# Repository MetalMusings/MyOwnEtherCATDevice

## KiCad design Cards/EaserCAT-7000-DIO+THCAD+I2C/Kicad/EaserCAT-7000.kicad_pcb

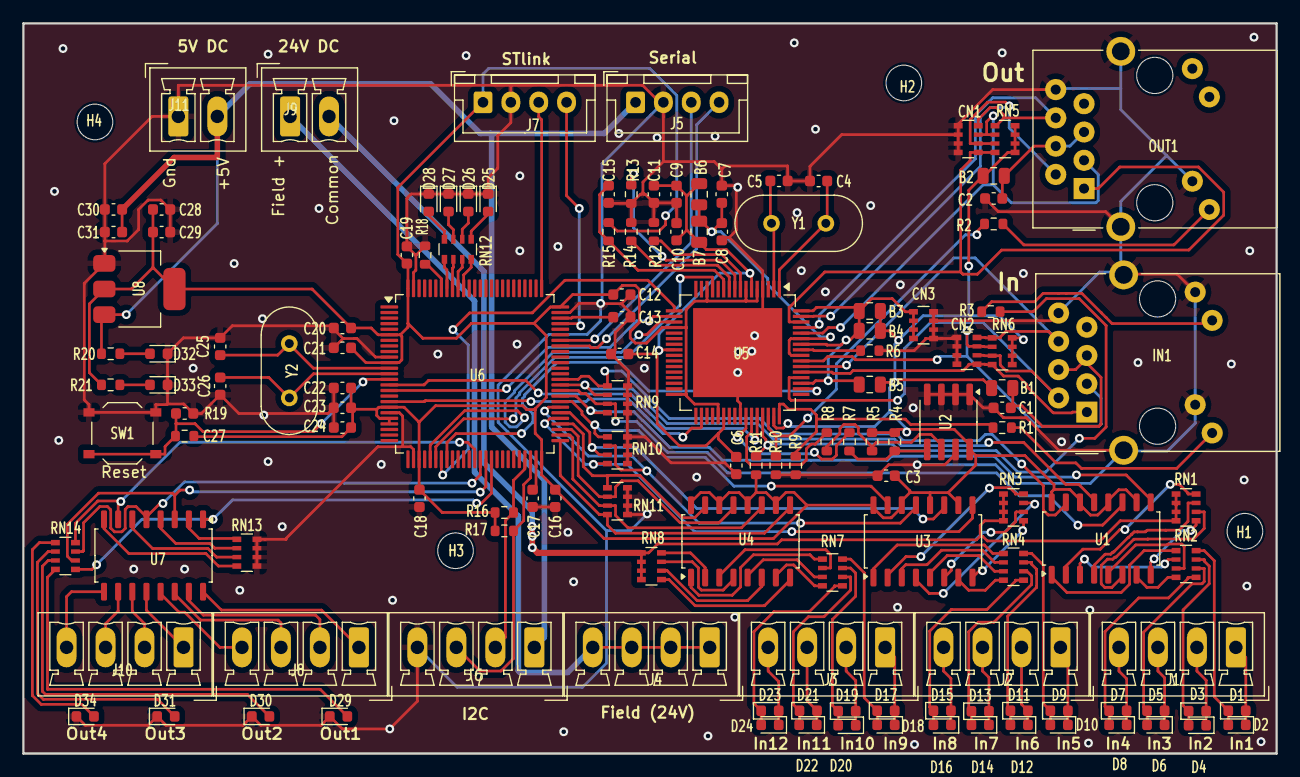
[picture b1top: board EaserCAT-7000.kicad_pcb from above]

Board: 2 copper layers, 112.5 x 65.6 mm, 138 parts (0 on the bottom side), 144 nets.

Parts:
B1, B2, B3, B4, B5, B6, B7: BLM18EG221S; C_0805_2012Metric
C1, C2, C3, C6, C8, C10, C12, C14, C15, C16, C18, C19, C20, C21, C22, C23, C24, C27, C29, C31: 0.1uF; C_0603_1608Metric
C4, C5: 20pF; C_0603_1608Metric
C7: 2uF; C_0603_1608Metric
C9: 1uF; C_0603_1608Metric
C11: 470pF; C_0603_1608Metric
C13, C17: 2.2uF; C_0603_1608Metric
C25, C26: 22pF; C_0603_1608Metric
C28, C30: 10uF; C_0603_1608Metric
CN1, CN2: 10pF; R_Array_Convex_4x0603
CN3: 0.1uF; R_Array_Convex_4x0603
D1, D3, D5, D7, D9, D11, D13, D15, D17, D19, D21, D23: Yellow led; LED_0603_1608Metric
D2, D4, D6, D8, D10, D12, D14, D16, D18, D20, D22, D24, D27: Red led; LED_0603_1608Metric
D25: Green led; LED_0603_1608Metric
D26: Orange led; LED_0603_1608Metric
D28: Blue led; LED_0603_1608Metric
D29, D30, D31, D34: White; LED_0603_1608Metric
D32, D33: Blue; LED_0603_1608Metric
H1, H2, H3, H4: MountingHole; MountingHole_3.2mm_M3_ISO14580
IN1: J0011D01BNL; PulseJack JB0011D01BNL
J1: In1-4; PhoenixContact_MCV_1,5_4-G-3.5_1x04_P3.50mm_Vertical
J2: In5-8; PhoenixContact_MCV_1,5_4-G-3.5_1x04_P3.50mm_Vertical
J3: In9-12; PhoenixContact_MCV_1,5_4-G-3.5_1x04_P3.50mm_Vertical
J4: 24V_Common; PhoenixContact_MCV_1,5_4-G-3.5_1x04_P3.50mm_Vertical
J5: Serial usart1; JST_XH_B4B-XH-A_1x04_P2.50mm_Vertical
J6: I2C; PhoenixContact_MCV_1,5_4-G-3.5_1x04_P3.50mm_Vertical
J7: STLINK; JST_XH_B4B-XH-A_1x04_P2.50mm_Vertical
J8: Output1-2; PhoenixContact_MCV_1,5_4-G-3.5_1x04_P3.50mm_Vertical
J9: 24V Field; PhoenixContact_MCV_1,5_2-G-3.5_1x02_P3.50mm_Vertical
J10: Output3-4; PhoenixContact_MCV_1,5_4-G-3.5_1x04_P3.50mm_Vertical
J11: 5V input; PhoenixContact_MCV_1,5_2-G-3.5_1x02_P3.50mm_Vertical
OUT1: J0011D01BNL; PulseJack JB0011D01BNL
R1, R2, R3, R19: 1k; R_0603_1608Metric
R4, R5, R16, R17, R21: 2k; R_0603_1608Metric
R6: 12.1k; R_0603_1608Metric
R7, R8: 22; R_0603_1608Metric
R9, R10, R11, R12, R13, R14, R15: 10k; R_0603_1608Metric
R18: 100k; R_0603_1608Metric
R20: 4k7; R_0603_1608Metric
RN1, RN3, RN8, RN12: 1k; R_Array_Convex_4x0603
RN2, RN4, RN7, RN14: 4k7; R_Array_Convex_4x0603
RN5, RN6: 49.9; R_Array_Convex_4x0603
RN9, RN10, RN11: 39k; R_Array_Convex_4x0603
RN13: 330; R_Array_Convex_4x0603
SW1: SW_Push; SW_Push_1P1T_XKB_TS-1187A
U1, U3, U4, U7: TLP292-4; SOIC-16_4.55x10.3mm_P1.27mm
U2: AT24CS32-SSHM; SOIC-8_3.9x4.9mm_P1.27mm
U5: LAN9252_PT; TQFP-64-1EP_10x10mm_P0.5mm_EP8x8mm
U6: STM32F407VGT6; LQFP-100_14x14mm_P0.5mm
U8: AMS1117-3.3; SOT-223-3_TabPin2
Y1: 25MHz; Crystal_HC49-4H_Vertical
Y2: 8 MHz; Crystal_HC49-4H_Vertical

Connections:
24V_COMMON: J9.2, RN1.5 (R4.2), RN1.6 (R3.2), RN1.7 (R2.2), RN1.8 (R1.2), RN3.5 (R4.2), RN3.6 (R3.2), RN3.7 (R2.2), RN3.8 (R1.2), RN8.5 (R4.2), RN8.6 (R3.2), RN8.7 (R2.2), RN8.8 (R1.2)
24V_FIELD: J4.1, J4.2, J4.3, J4.4, J9.1
+1V2: B6.1, B7.1, C6.2, C9.1, C10.2, C11.1, C14.2, U5.6 (VDDCR), U5.24 (VDDCR), U5.38 (VDDCR)
+3.3V: B1.1, B2.1, B3.1, B4.1, B5.1, C3.2, C12.1, C16.1, C18.1, C19.1, C20.1, C21.1, C22.1, C23.1, C24.1, C28.1, C29.1, J7.1, R4.1, R5.1, R11.1, R15.1, R16.1, R17.1, R19.2, R21.1, RN5.1 (R1.1), RN5.2 (R2.1), RN5.3 (R3.1), RN5.4 (R4.1), RN6.1 (R1.1), RN6.2 (R2.1), RN6.3 (R3.1), RN6.4 (R4.1), U1.10, U1.12, U1.14, U1.16, U2.8 (VCC), U3.10, U3.12, U3.14, U3.16, U4.10, U4.12, U4.14, U4.16, U5.5 (VDD33), U5.7 (REG_EN), U5.14 (VDDIO), U5.20 (VDDIO), U5.32 (VDDIO), U5.37 (VDDIO), U5.47 (VDDIO), U6.6 (VBAT), U6.11 (VDD), U6.19 (VDD), U6.21 (VREF+), U6.22 (VDDA), U6.28 (VDD), U6.50 (VDD), U6.75 (VDD), U6.100 (VDD), U8.2 (VO)
+3.3VA: B3.2, B4.2, B5.2, CN3.1 (R1.1), CN3.2 (R2.1), CN3.3 (R3.1), CN3.4 (R4.1), U5.51 (VDD33TXRX1), U5.58 (VDD33BIAS), U5.64 (VDD33TXRX2)
+5V: C30.1, C31.1, J5.1, J6.1, J11.2, R20.1, U8.3 (VI)
FXLOSA: R13.1, U5.9 (FXSDA/FXLOSA/~FXSDENA)
FXLOSB: R14.1, U5.10 (FXSDB/FXLOSB/~FXSDENB)
FXLOSEN: R12.1, U5.8 (~FXLOSEN)
GND: C1.1, C2.1, C3.1, C4.1, C5.1, C6.1, C7.2, C8.2, C9.2, C10.1, C11.2, C12.2, C13.1, C14.1, C15.1, C16.2, C17.1, C18.2, C19.2, C20.2, C21.2, C22.2, C23.2, C24.2, C25.1, C26.1, C27.1, C28.2, C29.2, C30.2, C31.2, CN1.5 (R4.2), CN1.6 (R3.2), CN1.7 (R2.2), CN1.8 (R1.2), CN2.5 (R4.2), CN2.6 (R3.2), CN2.7 (R2.2), CN2.8 (R1.2), CN3.5 (R4.2), CN3.6 (R3.2), CN3.7 (R2.2), CN3.8 (R1.2), D25.1 (K), D26.1 (K), D27.1 (K), D28.1 (K), D29.1 (K), D30.1 (K), D31.1 (K), D32.1 (K), D33.1 (K), D34.1 (K), IN1.8 (CHS_GND), IN1.10, IN1.12, IN1.SH (CHS_GND), J5.2, J6.4, J7.2, J11.1, OUT1.8 (CHS_GND), OUT1.10, OUT1.SH (CHS_GND), R6.1, R9.2, R10.2, R12.2, R13.2, R14.2, R18.1, RN9.5 (R4.2), RN9.6 (R3.2), RN9.7 (R2.2), RN9.8 (R1.2), RN10.5 (R4.2), RN10.6 (R3.2), RN10.7 (R2.2), RN10.8 (R1.2), RN11.5 (R4.2), RN11.6 (R3.2), RN11.7 (R2.2), RN11.8 (R1.2), RN13.5 (R4.2), RN13.6 (R3.2), RN13.7 (R2.2), RN13.8 (R1.2), SW1.1, U2.1 (A0), U2.2 (A1), U2.3 (A2), U2.4 (GND), U2.7 (WP), U5.4 (OSCVSS), U5.41 (TESTMODE), U5.65 (VSS), U6.10 (VSS), U6.20 (VSSA), U6.27 (VSS), U6.74 (VSS), U6.99 (VSS), U8.1 (GND)
I2C2_SCL: J6.2, R16.2, U6.47 (PB10)
I2C2_SDA: J6.3, R17.2, U6.48 (PB11)
I2C_SCL: R8.1, U5.43 (EESCL/TCK)
I2C_SDA: R7.1, U5.42 (EESDA/TMS)
IN0: RN9.1 (R1.1), U1.15, U6.62 (PD15)
IN1: RN9.2 (R2.1), U1.13, U6.61 (PD14)
IN2: RN9.3 (R3.1), U1.11, U6.60 (PD13)
IN3: RN9.4 (R4.1), U1.9, U6.59 (PD12)
IN4: RN10.1 (R1.1), U3.15, U6.58 (PD11)
IN5: RN10.2 (R2.1), U3.13, U6.57 (PD10)
IN6: RN10.3 (R3.1), U3.11, U6.56 (PD9)
IN7: RN10.4 (R4.1), U3.9, U6.55 (PD8)
IN8: RN11.1 (R1.1), U4.15, U6.54 (PB15)
IN9: RN11.2 (R2.1), U4.13, U6.53 (PB14)
IN10: RN11.3 (R3.1), U4.11, U6.52 (PB13)
IN11: RN11.4 (R4.1), U4.9, U6.51 (PB12)
IRQ: U5.44 (IRQ), U6.15 (PC0)
LINKACTLED0: R1.1, R9.1, U5.48 (LINKACTLED0/TDO/~CHIP_MODE0)
LINKACTLED1: R2.1, R10.1, U5.46 (LINKACTLED1/TDI/~CHIP_MODE1)
unnamed: D1.2 (A), D2.1 (K), J1.1
unnamed: D1.1 (K), D2.2 (A), RN2.8 (R1.2)
unnamed: D3.2 (A), D4.1 (K), J1.2
unnamed: D3.1 (K), D4.2 (A), RN2.7 (R2.2)
unnamed: D5.2 (A), D6.1 (K), J1.3
unnamed: D5.1 (K), D6.2 (A), RN2.6 (R3.2)
unnamed: D7.2 (A), D8.1 (K), J1.4
unnamed: D7.1 (K), D8.2 (A), RN2.5 (R4.2)
unnamed: D9.1 (K), D10.2 (A), RN4.8 (R1.2)
unnamed: D9.2 (A), D10.1 (K), J2.1
unnamed: D11.2 (A), D12.1 (K), J2.2
unnamed: D11.1 (K), D12.2 (A), RN4.7 (R2.2)
unnamed: D13.2 (A), D14.1 (K), J2.3
unnamed: D13.1 (K), D14.2 (A), RN4.6 (R3.2)
unnamed: D15.2 (A), D16.1 (K), J2.4
unnamed: D15.1 (K), D16.2 (A), RN4.5 (R4.2)
unnamed: D17.2 (A), D18.1 (K), J3.1
unnamed: D17.1 (K), D18.2 (A), RN7.8 (R1.2)
unnamed: D19.2 (A), D20.1 (K), J3.2
unnamed: D19.1 (K), D20.2 (A), RN7.7 (R2.2)
unnamed: D21.2 (A), D22.1 (K), J3.3
unnamed: D21.1 (K), D22.2 (A), RN7.6 (R3.2)
unnamed: D23.2 (A), D24.1 (K), J3.4
unnamed: D23.1 (K), D24.2 (A), RN7.5 (R4.2)
unnamed: D25.2 (A), RN12.5 (R4.2)
unnamed: D26.2 (A), RN12.6 (R3.2)
unnamed: D27.2 (A), RN12.7 (R2.2)
unnamed: D28.2 (A), RN12.8 (R1.2)
unnamed: D34.2 (A), RN14.5 (R4.2)
unnamed: D31.2 (A), RN14.6 (R3.2)
unnamed: D30.2 (A), RN14.7 (R2.2)
unnamed: D32.2 (A), R20.2
unnamed: D33.2 (A), R21.2
unnamed: D29.2 (A), RN14.8 (R1.2)
unnamed: IN1.9, R1.2
unnamed: IN1.11, R3.2
unnamed: B1.2, C1.2, IN1.4 (TCT), IN1.5 (RCT)
unnamed: J8.1, U7.16
unnamed: J8.2, U7.15
unnamed: J8.3, U7.14
unnamed: J8.4, U7.13
unnamed: J10.1, U7.12
unnamed: J10.2, U7.11
unnamed: J10.3, U7.10
unnamed: J10.4, U7.9
unnamed: OUT1.9, R2.2
unnamed: B2.2, C2.2, OUT1.4 (TCT), OUT1.5 (RCT)
unnamed: RN1.1 (R1.1), U1.8
unnamed: RN1.2 (R2.1), U1.6
unnamed: RN1.3 (R3.1), U1.4
unnamed: RN1.4 (R4.1), U1.2
unnamed: RN2.1 (R1.1), U1.1
unnamed: RN2.2 (R2.1), U1.3
unnamed: RN2.3 (R3.1), U1.5
unnamed: RN2.4 (R4.1), U1.7
unnamed: RN3.1 (R1.1), U3.8
unnamed: RN3.2 (R2.1), U3.6
unnamed: RN3.3 (R3.1), U3.4
unnamed: RN3.4 (R4.1), U3.2
unnamed: RN4.1 (R1.1), U3.1
unnamed: RN4.2 (R2.1), U3.3
unnamed: RN4.3 (R3.1), U3.5
unnamed: RN4.4 (R4.1), U3.7
unnamed: RN7.1 (R1.1), U4.1
unnamed: RN7.2 (R2.1), U4.3
unnamed: RN7.3 (R3.1), U4.5
unnamed: RN7.4 (R4.1), U4.7
unnamed: RN8.1 (R1.1), U4.8
unnamed: RN8.2 (R2.1), U4.6
unnamed: RN8.3 (R3.1), U4.4
unnamed: RN8.4 (R4.1), U4.2
unnamed: RN12.1 (R1.1), U6.93 (PB7)
unnamed: RN12.2 (R2.1), U6.92 (PB6)
unnamed: RN12.3 (R3.1), U6.91 (PB5)
unnamed: RN12.4 (R4.1), U6.90 (PB4)
unnamed: RN13.1 (R1.1), U7.2
unnamed: RN13.2 (R2.1), U7.4
unnamed: RN13.3 (R3.1), U7.6
unnamed: RN13.4 (R4.1), U7.8
unnamed: R5.2, R8.2, U2.6 (SCL)
unnamed: R4.2, R7.2, U2.5 (SDA)
unnamed: C4.2, U5.1 (OSCI), Y1.2
unnamed: C5.2, U5.2 (OSCO), Y1.1
unnamed: R6.2, U5.57 (RBIAS)
unnamed: C15.2, R15.2, U5.11 (~RST)
unnamed: R18.2, U6.94 (BOOT0)
unnamed: C27.2, R19.1, SW1.2, U6.14 (NRST)
unnamed: C25.2, U6.12 (PH0), Y2.2
unnamed: C26.2, U6.13 (PH1), Y2.1
unnamed: C17.2, U6.49 (VCAP_1)
unnamed: C13.2, U6.73 (VCAP_2)
OUT12: RN14.1 (R1.1), U6.41 (PE10), U7.1
OUT13: RN14.2 (R2.1), U6.40 (PE9), U7.3
OUT14: RN14.3 (R3.1), U6.39 (PE8), U7.5
OUT15: RN14.4 (R4.1), U6.38 (PE7), U7.7
RUNLED: R3.1, R11.2, U5.45 (RUNLED/~E2PSIZE)
RX: J5.3, U6.69 (PA10)
RXNA: CN2.4 (R4.1), IN1.6 (RD-), RN6.5 (R4.2), U5.54 (RXNA)
RXNB: CN1.4 (R4.1), OUT1.6 (RD-), RN5.5 (R4.2), U5.61 (RXNB)
RXPA: CN2.3 (R3.1), IN1.3 (RD+), RN6.6 (R3.2), U5.55 (RXPA)
RXPB: CN1.3 (R3.1), OUT1.3 (RD+), RN5.6 (R3.2), U5.60 (RXPB)
SPI_CS: U5.50 (D5/AD5/OUTVALID/SCS#), U6.33 (PC4)
SPI_MISO: U5.13 (D1/AD1/EOF/SO/SIO1), U6.31 (PA6)
SPI_MOSI: U5.17 (D0/AD0/WD_STATE/SI/SIO0), U6.32 (PA7)
SPI_SCK: U5.19 (D9/AD9/LATCH_IN/SCK), U6.30 (PA5)
SWCLK: J7.3, U6.76 (PA14)
SWDIO: J7.4, U6.72 (PA13)
SYNC0: U5.34 (SYNC0/LATCH0), U6.18 (PC3)
SYNC1: U5.18 (SYNC1/LATCH1), U6.16 (PC1)
TX: J5.4, U6.68 (PA9)
TXNA: CN2.2 (R2.1), IN1.2 (TD-), RN6.7 (R2.2), U5.52 (TXNA)
TXNB: CN1.2 (R2.1), OUT1.2 (TD-), RN5.7 (R2.2), U5.63 (TXNB)
TXPA: CN2.1 (R1.1), IN1.1 (TD+), RN6.8 (R1.2), U5.53 (TXPA)
TXPB: CN1.1 (R1.1), OUT1.1 (TD+), RN5.8 (R1.2), U5.62 (TXPB)
VDD12TX1: B6.2, B7.2, C7.1, C8.1, U5.56 (VDD12TX1), U5.59 (VDD12TX2)

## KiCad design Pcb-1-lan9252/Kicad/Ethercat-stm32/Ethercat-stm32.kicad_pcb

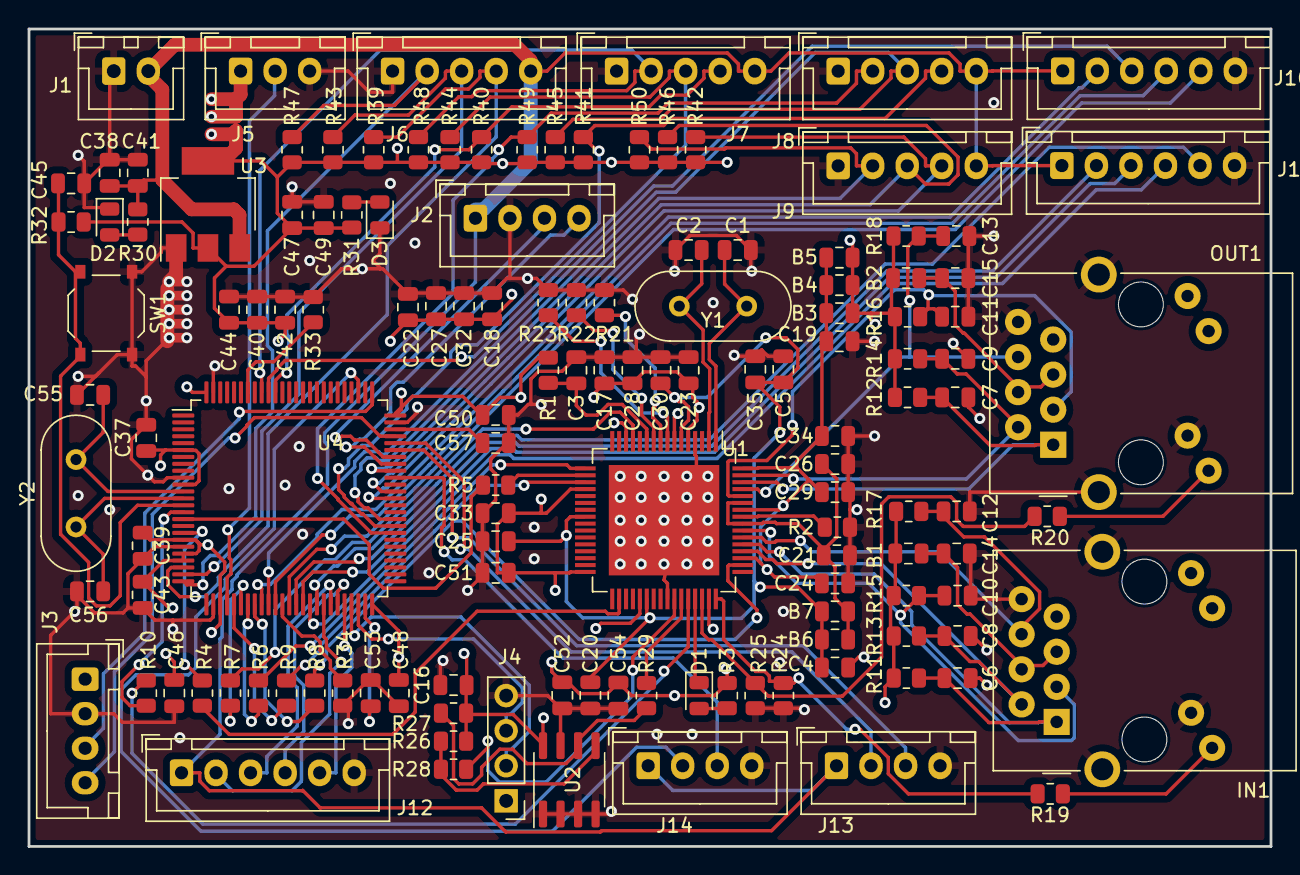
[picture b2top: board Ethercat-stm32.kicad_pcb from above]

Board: 4 copper layers, 89.9 x 59.2 mm, 134 parts (0 on the bottom side), 91 nets.

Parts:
B1, B2: BLM18EG221S; C_0805_2012Metric
B3, B4, B5, B6, B7: BLM18EG221SN1D; C_0805_2012Metric
C1, C2: 20pF; C_0805_2012Metric
C3, C14, C15, C16, C17, C18, C19, C20, C21, C22, C23, C24, C25, C26, C27, C28, C29, C30, C32, C33, C34, C35, C37, C38, C39, C40, C42, C43, C44, C45, C46, C47, C48, C50, C51, C52, C54: 0.1uF; C_0805_2012Metric
C4: 470pF; C_0805_2012Metric
C5: 1uF; C_0805_2012Metric
C6, C7, C8, C9, C10, C11, C12, C13: 10pF; C_0805_2012Metric
C41, C49: 10uF; C_0805_2012Metric
C53, C57: 2.2uF; C_0805_2012Metric
C55, C56: 22pF; C_0805_2012Metric
D1: Green led; LED_0805_2012Metric
D2, D3: Blue led; LED_0805_2012Metric
IN1: J0011D01BNL; PulseJack JB0011D01BNL
J1: Conn_01x02_Pin; JST_XH_B2B-XH-A_1x02_P2.50mm_Vertical
J2: Serial usart1; JST_XH_B4B-XH-A_1x04_P2.50mm_Vertical
J3: STLINK; JST_XH_B4B-XH-A_1x04_P2.50mm_Vertical
J4: I2C bus2; PinHeader_1x04_P2.54mm_Vertical
J5: DAC1; JST_XH_B3B-XH-A_1x03_P2.50mm_Vertical
J6: Encoder 1; JST_XH_B5B-XH-A_1x05_P2.50mm_Vertical
J7: Encoder 2; JST_XH_B5B-XH-A_1x05_P2.50mm_Vertical
J8: Encoder 3; JST_XH_B5B-XH-A_1x05_P2.50mm_Vertical
J9: Encoder 4; JST_XH_B5B-XH-A_1x05_P2.50mm_Vertical
J10, J11, J12: Conn_01x06_Pin; JST_XH_B6B-XH-A_1x06_P2.50mm_Vertical
J13: Stepper 1; JST_XH_B4B-XH-A_1x04_P2.50mm_Vertical
J14: Stepper 2; JST_XH_B4B-XH-A_1x04_P2.50mm_Vertical
OUT1: J0011D01BNL; PulseJack JB0011D01BNL
R1, R21, R22, R23, R24, R25: 10k; R_0805_2012Metric
R2: 12.1k; R_0805_2012Metric
R3, R19, R20, R30, R31, R32, R39, R40, R41, R42, R43, R44, R45, R46, R47, R48, R49, R50: 1k; R_0805_2012Metric
R4, R5, R6, R7, R8, R9, R10, R28, R29, R33, R34: 22; R_0805_2012Metric
R11, R12, R13, R14, R15, R16, R17, R18: 49.9; R_0805_2012Metric
R26, R27: 2k; R_0805_2012Metric
SW1: SW_Push; SW_Push_1P1T_XKB_TS-1187A
U1: LAN9252_PT; TQFP-64-1EP_10x10mm_P0.5mm_EP8x8mm
U2: AT24CS32-SSHM; SOIC-8_3.9x4.9mm_P1.27mm
U3: AMS1117-3.3; SOT-223-3_TabPin2
U4: STM32F407VGT6; LQFP-100_14x14mm_P0.5mm
Y1: 25MHz; Crystal_HC49-U_Vertical
Y2: 8 MHz; Crystal_HC49-U_Vertical

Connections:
+1V2: B6.1, B7.1, C4.1, C5.1, C20.1, C25.1, C30.1, C35.1, U1.6 (VDDCR), U1.24 (VDDCR), U1.38 (VDDCR)
+3.3V: B1.1, B2.1, B3.1, B4.1, B5.1, C16.2, C17.1, C18.1, C22.1, C23.1, C27.1, C28.1, C32.1, C33.1, C37.1, C39.1, C40.1, C42.1, C43.1, C44.1, C46.1, C47.1, C48.1, C49.1, C50.1, C51.1, C52.1, C54.1, J3.1, J4.1, J5.1, R1.1, R3.1, R11.2, R12.2, R13.2, R14.2, R15.2, R16.2, R17.2, R18.2, R26.1, R27.1, R31.2, R32.2, R39.2, R40.2, R41.2, R42.2, R43.2, R44.2, R45.2, R46.2, R47.2, R48.2, R49.2, R50.2, U1.5 (VDD33), U1.7 (REG_EN), U1.14 (VDDIO), U1.20 (VDDIO), U1.32 (VDDIO), U1.37 (VDDIO), U1.47 (VDDIO), U2.8 (VCC), U3.2 (VO), U4.6 (VBAT), U4.11 (VDD), U4.19 (VDD), U4.21 (VREF+), U4.22 (VDDA), U4.28 (VDD), U4.50 (VDD), U4.75 (VDD), U4.100 (VDD)
+3.3VA: B3.2, B4.2, B5.2, C19.1, C24.1, C29.1, C34.1, U1.51 (VDD33TXRX1), U1.58 (VDD33BIAS), U1.64 (VDD33TXRX2)
+5V: C38.1, C41.1, J1.2, J2.1, J6.5, J7.5, J8.5, J9.5, J10.1, J11.1, J12.1, J13.1, J14.1, R30.2, U3.3 (VI)
/STM32F4/BOOT1: R34.2, U4.37 (PB2)
DAC1: J5.2, U4.29 (PA4)
ENC1_A: J6.4, R39.1, U4.23 (PA0)
ENC1_B: J6.3, R43.1, U4.24 (PA1)
ENC1_Z: J6.2, R47.1, U4.25 (PA2)
ENC2_A: J7.4, R40.1, U4.90 (PB4)
ENC2_B: J7.3, R44.1, U4.91 (PB5)
ENC2_Z: J7.2, R48.1, U4.92 (PB6)
ENC3_A: J8.4, R41.1, U4.59 (PD12)
ENC3_B: J8.3, R45.1, U4.60 (PD13)
ENC3_Z: J8.2, R49.1, U4.58 (PD11)
ENC4_A: J9.4, R42.1, U4.63 (PC6)
ENC4_B: J9.3, R46.1, U4.64 (PC7)
ENC4_Z: J9.2, R50.1, U4.67 (PA8)
FXLOSA: R21.1, U1.9 (FXSDA/FXLOSA/~FXSDENA)
FXLOSB: R22.1, U1.10 (FXSDB/FXLOSB/~FXSDENB)
FXLOSEN: R23.1, U1.8 (~FXLOSEN)
GND: C1.1, C2.1, C3.1, C4.2, C5.2, C6.1, C7.1, C8.1, C9.1, C10.1, C11.1, C12.1, C13.1, C14.1, C15.1, C16.1, C17.2, C18.2, C19.2, C20.2, C21.2, C22.2, C23.2, C24.2, C25.2, C26.2, C27.2, C28.2, C29.2, C30.2, C32.2, C33.2, C34.2, C35.2, C37.2, C38.2, C39.2, C40.2, C41.2, C42.2, C43.2, C44.2, C45.1, C46.2, C47.2, C48.2, C49.2, C50.2, C51.2, C52.2, C53.1, C54.2, C55.1, C56.1, C57.1, D2.1 (K), D3.1 (K), IN1.8 (CHS_GND), IN1.10, IN1.SH (CHS_GND), J1.1, J2.2, J3.2, J4.4, J5.3, J6.1, J7.1, J8.1, J9.1, J10.6, J11.6, J12.6, J13.4, J14.4, OUT1.8 (CHS_GND), OUT1.10, OUT1.SH (CHS_GND), R2.1, R21.2, R22.2, R23.2, R24.2, R25.2, R33.1, R34.1, SW1.1, U1.4 (OSCVSS), U1.41 (TESTMODE), U1.65 (VSS), U2.1 (A0), U2.2 (A1), U2.3 (A2), U2.4 (GND), U2.7 (WP), U3.1 (GND), U4.10 (VSS), U4.20 (VSSA), U4.27 (VSS), U4.74 (VSS), U4.99 (VSS)
GPIO0: R19.1, R24.1, U1.48 (LINKACTLED0/TDO/~CHIP_MODE0)
GPIO1: R20.1, R25.1, U1.46 (LINKACTLED1/TDI/~CHIP_MODE1)
I2C2_SCL: J4.2, U4.47 (PB10)
I2C2_SDA: J4.3, U4.48 (PB11)
I2C_SCL: R29.1, U1.43 (EESCL/TCK)
I2C_SDA: R28.1, U1.42 (EESDA/TMS)
IO1: J10.2, U4.34 (PC5)
IO2: J10.3, U4.35 (PB0)
IO3: J10.4, U4.36 (PB1)
IO4: J10.5, U4.38 (PE7)
IO5: J11.2, U4.39 (PE8)
IO6: J11.3, U4.40 (PE9)
IO7: J11.4, U4.41 (PE10)
IO8: J11.5, U4.42 (PE11)
IO9: J12.2, U4.43 (PE12)
IO10: J12.3, U4.44 (PE13)
IO11: J12.4, U4.45 (PE14)
IO12: J12.5, U4.46 (PE15)
IRQ: R10.1, U4.15 (PC0)
NRST: C45.2, R32.1, SW1.2, U4.14 (NRST)
unnamed: D1.2 (A), R3.2
unnamed: D1.1 (K), U1.45 (RUNLED/~E2PSIZE)
unnamed: D2.2 (A), R30.1
unnamed: D3.2 (A), R31.1
unnamed: IN1.9, R19.2
unnamed: B1.2, C14.2, IN1.4 (TCT), IN1.5 (RCT)
unnamed: OUT1.9, R20.2
unnamed: B2.2, C15.2, OUT1.4 (TCT), OUT1.5 (RCT)
unnamed: R6.2, U1.17 (D0/AD0/WD_STATE/SI/SIO0)
unnamed: R7.2, U1.13 (D1/AD1/EOF/SO/SIO1)
unnamed: R8.2, U1.50 (D5/AD5/OUTVALID/SCS#)
unnamed: R9.2, U1.19 (D9/AD9/LATCH_IN/SCK)
unnamed: R10.2, U1.44 (IRQ)
unnamed: C1.2, U1.1 (OSCI), Y1.2
unnamed: C2.2, U1.2 (OSCO), Y1.1
unnamed: R2.2, U1.57 (RBIAS)
unnamed: R4.1, U1.34 (SYNC0/LATCH0)
unnamed: R5.1, U1.18 (SYNC1/LATCH1)
unnamed: C3.2, R1.2, U1.11 (~RST)
unnamed: R27.2, R29.2, U2.6 (SCL)
unnamed: R26.2, R28.2, U2.5 (SDA)
unnamed: R33.2, U4.94 (BOOT0)
unnamed: C55.2, U4.12 (PH0), Y2.2
unnamed: C56.2, U4.13 (PH1), Y2.1
unnamed: C53.2, U4.49 (VCAP_1)
unnamed: C57.2, U4.73 (VCAP_2)
RX: J2.3, U4.69 (PA10)
RXNA: C12.2, IN1.6 (RD-), R17.1, U1.54 (RXNA)
RXNB: C13.2, OUT1.6 (RD-), R18.1, U1.61 (RXNB)
RXPA: C10.2, IN1.3 (RD+), R15.1, U1.55 (RXPA)
RXPB: C11.2, OUT1.3 (RD+), R16.1, U1.60 (RXPB)
SPI_CS: R8.1, U4.33 (PC4)
SPI_MISO: R7.1, U4.31 (PA6)
SPI_MOSI: R6.1, U4.32 (PA7)
SPI_SCK: R9.1, U4.30 (PA5)
STEP1_DIR: J13.2, U4.71 (PA12)
STEP1_STEP: J13.3, U4.70 (PA11)
STEP2_DIR: J14.2, U4.78 (PC10)
STEP2_STEP: J14.3, U4.66 (PC9)
SWCLK: J3.3, U4.76 (PA14)
SWDIO: J3.4, U4.72 (PA13)
SYNC0: R4.2, U4.18 (PC3)
SYNC1: R5.2, U4.16 (PC1)
TX: J2.4, U4.68 (PA9)
TXNA: C8.2, IN1.2 (TD-), R13.1, U1.52 (TXNA)
TXNB: C9.2, OUT1.2 (TD-), R14.1, U1.63 (TXNB)
TXPA: C6.2, IN1.1 (TD+), R11.1, U1.53 (TXPA)
TXPB: C7.2, OUT1.1 (TD+), R12.1, U1.62 (TXPB)
VDD12TX1: B6.2, B7.2, C21.1, C26.1, U1.56 (VDD12TX1), U1.59 (VDD12TX2)
